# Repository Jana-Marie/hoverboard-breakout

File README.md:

# Hoverboard breakout boards

### [Bobbycar breakout](/bobbycar_breakout/)

Hoverboard breakout board for Bobbycars, features a PCB-Nunchuk connector, a linear regulator, pull-ups for I2C and pull-downs for ADC-input

### [Nunchuk breakout](/nunchuk_breakout/)

Nunchuk to hoverboard connector board, features a Nunchuk socket, a linear regulator and pullups. This board is only intended for nunchuk use, therefore it is smaller and features the fitting socket.

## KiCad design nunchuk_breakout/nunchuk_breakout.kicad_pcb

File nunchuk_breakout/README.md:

# hoverboard-nunchuk-breakout

Hoverboard to nunchuk-connector breakout.

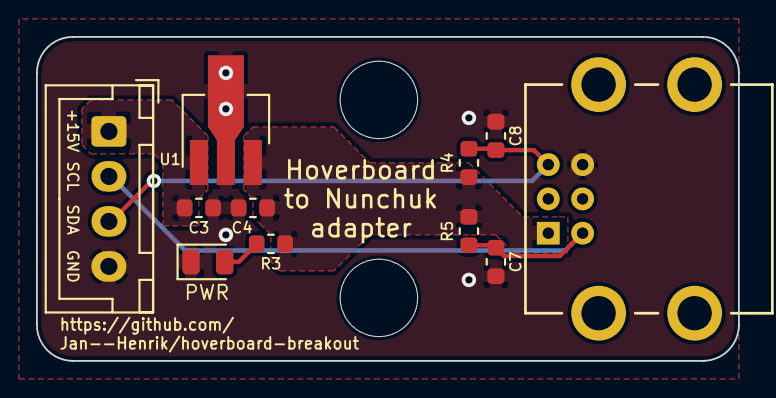
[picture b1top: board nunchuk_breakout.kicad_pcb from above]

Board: 2 copper layers, 39.0 x 18.0 mm, 13 parts (0 on the bottom side), 6 nets.

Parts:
C3, C4: 1uF; C_0603_1608Metric
C7, C8: 10p; C_0603_1608Metric
D3: LED; LED_0805_2012Metric
H1, H2: MountingHole; MountingHole_4.3mm_M4
J2: Conn_01x04; JST_XH_B04B-XH-A_1x04_P2.50mm_Vertical
P1: CONN_WII
R3: 220Ohm; R_0603_1608Metric
R4, R5: 3k3; R_0603_1608Metric
U1: L7805SOT89; SOT-89-3_Handsoldering

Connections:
GND: C3.2, C4.2, C7.1, C8.2, D3.1, J2.4, P1.6, U1.2
unnamed: D3.2, R3.1
SCL: C7.2, J2.2, P1.2, R5.2
SDA: C8.1, J2.3, P1.5, R4.2
VCC: C4.1, P1.1, R3.2, R4.1, R5.1, U1.3
VDD: C3.1, J2.1, U1.1

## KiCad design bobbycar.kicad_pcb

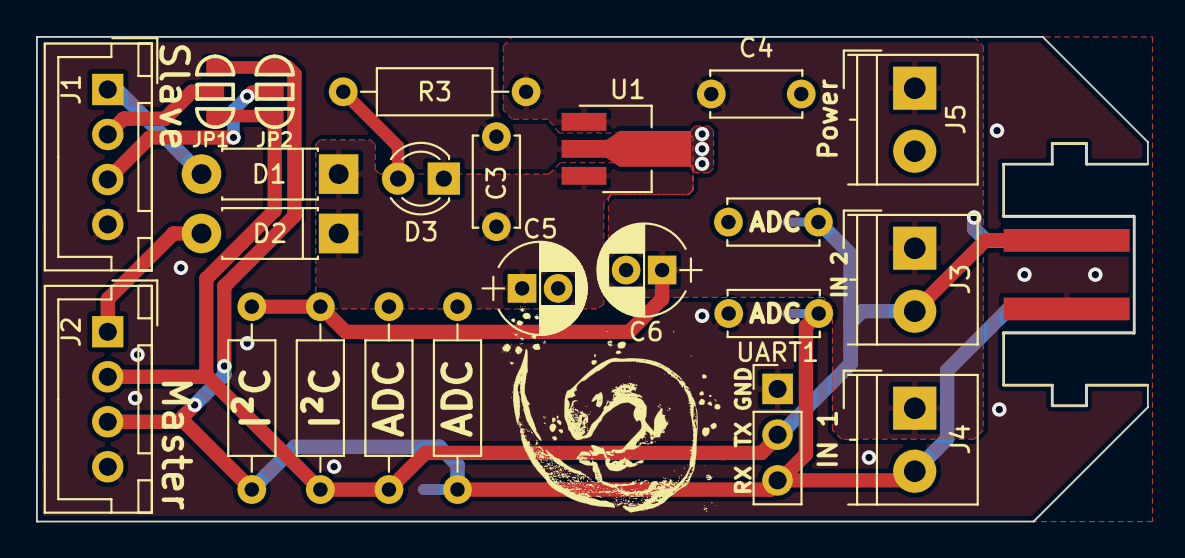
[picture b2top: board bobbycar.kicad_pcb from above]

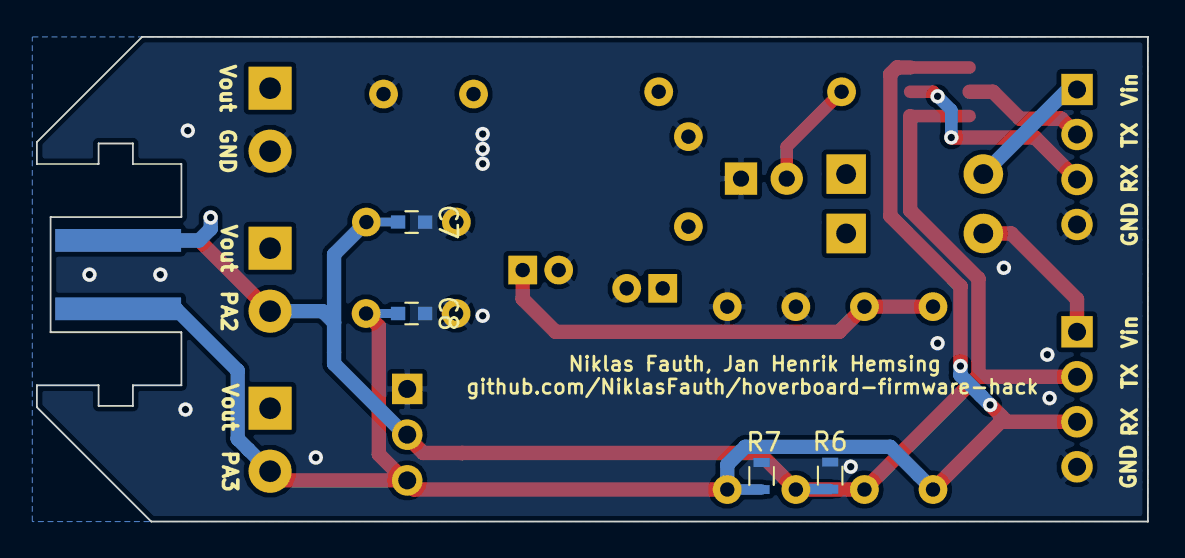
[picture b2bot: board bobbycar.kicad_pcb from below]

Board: 2 copper layers, 61.7 x 26.9 mm, 28 parts (4 on the bottom side), 10 nets.

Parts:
C1, C2: C_Small; C_Disc_D5.0mm_W2.5mm_P5.00mm
C3, C4: 1uF; C_Disc_D5.0mm_W2.5mm_P5.00mm
C5, C6: 22uF; CP_Radial_D5.0mm_P2.00mm
C7, C8: C_Small; C_0603
D1, D2: D; D_DO-41_SOD81_P7.62mm_Horizontal
D3: LED; LED_D3.0mm
J1, J2: Conn_01x04; JST_XH_B04B-XH-A_04x2.50mm_Straight
J3, J4, J5: Screw_Terminal_01x02; TerminalBlock_4UCON_19963_02x3.5mm_Straight
J6: Conn_01x04; NUNCHUCK
JP1, JP2: Jumper_NC_Dual; SOLDER-JUMPER_2-WAY
R1, R2: R_Small; R_Axial_DIN0207_L6.3mm_D2.5mm_P10.16mm_Horizontal
R3: 220Ohm; R_Axial_DIN0207_L6.3mm_D2.5mm_P10.16mm_Horizontal
R4, R5: 3k3; R_Axial_DIN0207_L6.3mm_D2.5mm_P10.16mm_Horizontal
R6, R7: R_Small; R_0603
U1: L7805SOT89; SOT-89-3_Handsoldering
UART1: Conn_01x03; Pin_Header_Straight_1x03_Pitch2.54mm

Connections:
GND: C1.1, C2.2, C3.2, C4.2, C5.2, C6.2, C7.1, C8.2, D3.1, J1.4, J2.4, J5.2, J6.1, R1.1, R2.2, R6.1, R7.2, U1.2, UART1.1
unnamed: D1.2, J1.1
unnamed: D2.2, J2.1
unnamed: D3.2, R3.1
RX: C2.1, C8.1, J2.3, J4.2, J6.4, JP1.3, JP2.3, R2.1, R4.2, R7.1, UART1.3
RX.1: J1.3, JP2.2
TX: C1.2, C7.2, J2.2, J3.2, J6.2, JP1.1, JP2.1, R1.2, R5.2, R6.2, UART1.2
TX.1: J1.2, JP1.2
VCC: C4.1, C6.1, J3.1, J4.1, J5.1, J6.3, R3.2, R4.1, R5.1, U1.1
VDD: C3.1, C5.1, D1.1, D2.1, U1.3

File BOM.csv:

"ID";"Bezeichner";"Gehäuse";"Stückzahl";"Bezeichnung";"Anbieter und Referenz";
1;"C2,C1";"C_Disc_D5.0mm_W2.5mm_P5.00mm";2;"100nF";;;
2;"C3,C4";"C_Disc_D5.0mm_W2.5mm_P5.00mm";2;"1uF";;;
3;"R2,R1";"R_Axial_DIN0207_L6.3mm_D2.5mm_P10.16mm_Horizontal";2;"To be calculated";;;
4;"R7,R6";"R_0603";2;"100nF";;;
5;"C7,C8";"C_0603";2;"100nF";;;
6;"D1,D2";"D_DO-41_SOD81_P7.62mm_Horizontal";2;"1N400x";;;
7;"U1";"SOT-89-3_Handsoldering";1;"L7805SOT89";;;
8;"UART1";"Pin_Header_Straight_1x03_Pitch2.54mm";1;"Conn_01x03";;;
9;"R3";"R_Axial_DIN0207_L6.3mm_D2.5mm_P10.16mm_Horizontal";1;"220Ohm";;;
10;"R4,R5";"R_Axial_DIN0207_L6.3mm_D2.5mm_P10.16mm_Horizontal";2;"3k3";;;
11;"C5,C6";"CP_Radial_D5.0mm_P2.00mm";2;"22uF";;;
12;"J1,J2";"JST_XH_B04B-XH-A_04x2.50mm_Straight";2;"JST PH";;;
13;"J4,J5,J3";"TerminalBlock_4UCON_19963_02x3.5mm_Straight";3;"Screw_Terminal_01x02";;;
14;"D3";"LED_D3.0mm";1;"LED";;;
15;"JP1,JP2";"SOLDER-JUMPER_2-WAY";2;"Jumper_NC_Dual";;;
16;"J6";"NUNCHUCK";1;"Conn_01x04";;;
17;"G***";"otterimage_crop_13";1;"LOGO";;;

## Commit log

2018-04-16 added KiCAD project files
2018-04-16 added gerber files
2018-04-16 added nunchuck library files
2018-04-16 added files of otter images :3
2018-04-16 added images
2018-06-26 UPDATED pcb files
2018-08-13 added gerber
2018-08-13 added BOM
2018-09-22 fixed library names
2018-12-28 added images of plugged nunchuck
2018-12-28 added images to readme
2019-01-02 moved V1 to V1 folder
2019-01-02 added V2
2019-01-02 added README
2019-01-02 added README to V1
2019-01-02 renamed folders
2019-01-02 moved kicad lib
2019-01-02 added image
2019-01-02 updated gerber
2019-01-02 updated PCB
2019-01-02 changed rendering
2019-01-04 Create LICENSE
2019-01-17 added panelized gerber (12/panel)
2019-02-24 added x3 gerber
2019-05-21 Add kitspace.yaml
2019-05-24 Fix bom csv headers for correct parsing
2019-06-02 Add site links to kitspace.yaml
2019-09-28 updated bom
2020-06-29 Updated Readme - added Jumper settings
2020-06-29 Added image of jumper settings
2020-08-22 Add kicad_pcb files to kitspace.yaml
2021-03-11 Remove duplicate gerber files
2022-01-18 updated to kicad 6
2022-10-03 Kitspace: have nunchuk panel and non-panel projects
2023-02-16 Add readme paths in kitspace.yaml
